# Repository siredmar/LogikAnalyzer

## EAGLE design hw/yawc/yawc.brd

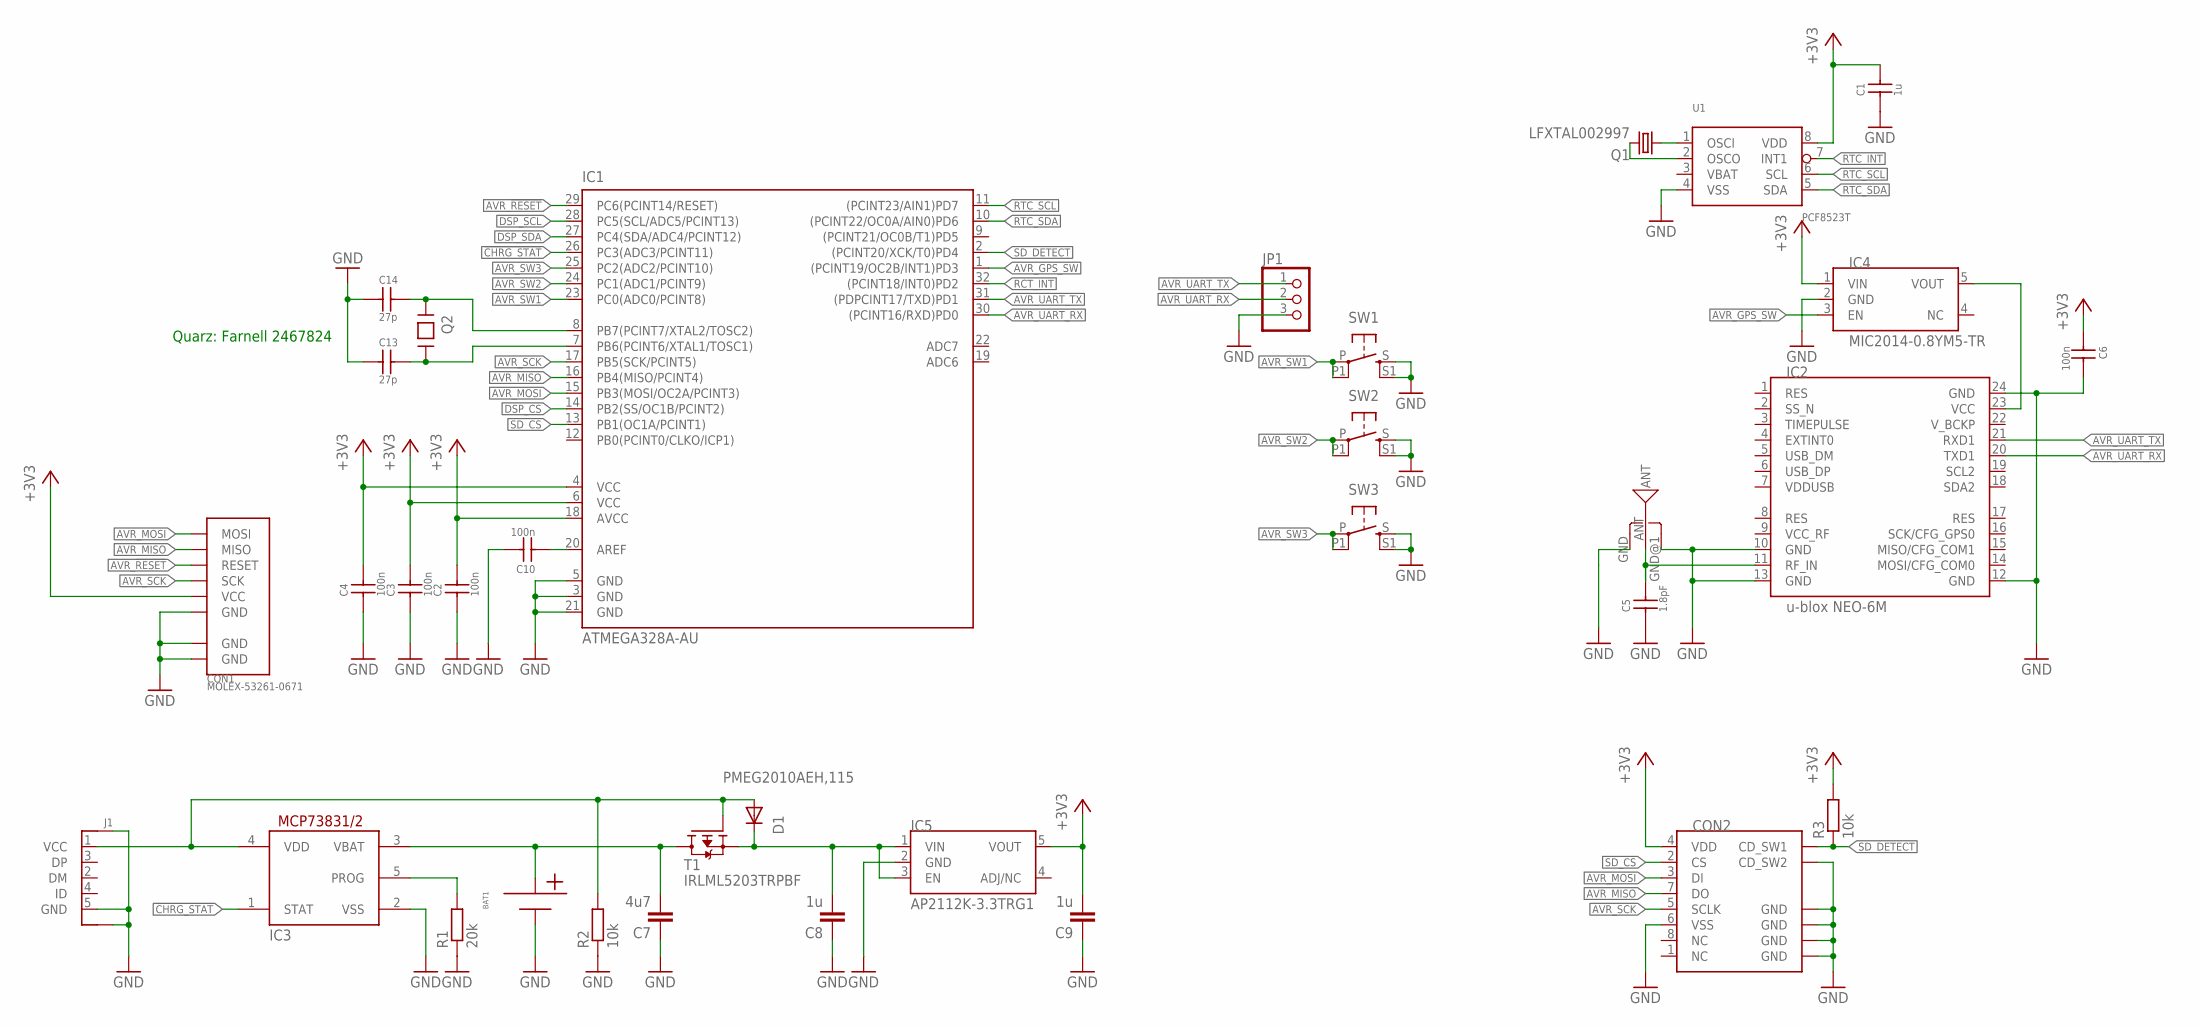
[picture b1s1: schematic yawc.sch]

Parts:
BAT1: LIPO_1S; LIPO_1S_SOLDER_CON
C1: 1u; C0603
C2, C3, C4, C6, C10: 100n; C0603
C5: 1.8pF; C0603
C7: 4u7; C0805
C8, C9: 1u; C0805
C13, C14: 27p; C0603
CON1: MOLEX-53261-0671
CON2: MICRO_SD_1140084168
D1: PMEG2010AEH,115; SOD123
IC1: ATMEGA328A-AU; TQFP32
IC2: u-blox NEO-6M; NEO-6
IC3: MCP73831/OT; SOT23-5L
IC4: MIC2014-0.8YM5-TR; SOT-23-5
IC5: AP2112K-3.3TRG1; SOT-23-5
J1: XM7D-0512
JP1: PINHD-1X3; 1X03
Q1: LFXTAL002997; TC26H
Q2: 16MHz; CRYSTAL-ABRACON-ABM7-SMD
R1: 20k; R0603
R2, R3: 10k; R0603
SW1, SW2, SW3: ALPS_SKHHLNA010
T1: IRLML5203TRPBF; SOT23
U1: PCF8523T; SOT96-1
U$1: ANT_W3011PULSE_1575MHZ; ANT4MMX4.25MM

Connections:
!CHRG_STAT: IC1.26 (PC3(ADC3/PCINT11)), IC3.1 (STAT)
+3V3: C1.2, C2.2, C3.2, C4.2, C6.1, C9.2, CON1.5 (VCC), CON2.4 (VDD), IC1.4 (VCC), IC1.6 (VCC), IC1.18 (AVCC), IC4.1 (VIN), IC5.5 (VOUT), R3.2, U1.8 (VDD)
AVR_!RESET: CON1.3 (RESET), IC1.29 (PC6(PCINT14/RESET))
AVR_GPS_SW: IC1.1 ((PCINT19/OC2B/INT1)PD3), IC4.3 (EN)
AVR_MISO: CON1.2 (MISO), CON2.7 (DO), IC1.16 (PB4(MISO/PCINT4))
AVR_MOSI: CON1.1 (MOSI), CON2.3 (DI), IC1.15 (PB3(MOSI/OC2A/PCINT3))
AVR_SCK: CON1.4 (SCK), CON2.5 (SCLK), IC1.17 (PB5(SCK/PCINT5))
AVR_SW1: IC1.23 (PC0(ADC0/PCINT8)), SW1.P, SW1.P1
AVR_SW2: IC1.24 (PC1(ADC1/PCINT9)), SW2.P, SW2.P1
AVR_SW3: IC1.25 (PC2(ADC2/PCINT10)), SW3.P, SW3.P1
AVR_UART_RX: IC1.30 ((PCINT16/RXD)PD0), IC2.20 (TXD1), JP1.2
AVR_UART_TX: IC1.31 ((PDPCINT17/TXD)PD1), IC2.21 (RXD1), JP1.1
DSP_CS: IC1.14 (PB2(SS/OC1B/PCINT2))
DSP_SCL: IC1.28 (PC5(SCL/ADC5/PCINT13))
DSP_SDA: IC1.27 (PC4(SDA/ADC4/PCINT12))
GND: BAT1.P$1 (+), C1.1, C2.1, C3.1, C4.1, C5.1, C6.2, C7.1, C8.1, C9.1, C10.2, C13.1, C14.1, CON1.6 (GND), CON1.GND@1 (GND), CON1.GND@2 (GND), CON2.6 (VSS), CON2.CD@2 (CD_SW2), CON2.GND@1 (GND), CON2.GND@2 (GND), CON2.GND@3 (GND), CON2.GND@4 (GND), IC1.3 (GND), IC1.5 (GND), IC1.21 (GND), IC2.10 (GND), IC2.12 (GND), IC2.13 (GND), IC2.24 (GND), IC3.2 (VSS), IC4.2 (GND), IC5.2 (GND), J1.5 (GND), J1.P$8 (GND), J1.P$9 (GND), JP1.3, R1.1, R2.1, SW1.S, SW1.S1, SW2.S, SW2.S1, SW3.S, SW3.S1, U1.4 (VSS), U$1.GND, U$1.GND@1 (GND)
unnamed: Q1.1, U1.1 (OSCI)
unnamed: Q1.2, U1.2 (OSCO)
unnamed: C5.2, IC2.11 (RF_IN), U$1.ANT
unnamed: C13.2, IC1.7 (PB6(PCINT6/XTAL1/TOSC1)), Q2.P$2
unnamed: C10.1, IC1.20 (AREF)
unnamed: C14.2, IC1.8 (PB7(PCINT7/XTAL2/TOSC2)), Q2.P$1
unnamed: IC2.23 (VCC), IC4.5 (VOUT)
unnamed: IC3.5 (PROG), R1.2
unnamed: D1.A, IC3.4 (VDD), J1.1 (VCC), R2.2, T1.1 (G)
unnamed: BAT1.P$2 (-), C7.2, IC3.3 (VBAT), T1.3 (D)
unnamed: C8.2, D1.C, IC5.1 (VIN), IC5.3 (EN), T1.2 (S)
RCT_INT: IC1.32 ((PCINT18/INT0)PD2)
RTC_INT: U1.7 (INT1)
RTC_SCL: IC1.11 ((PCINT23/AIN1)PD7), U1.6 (SCL)
RTC_SDA: IC1.10 ((PCINT22/OC0A/AIN0)PD6), U1.5 (SDA)
SD_CS: CON2.2 (CS), IC1.13 (PB1(OC1A/PCINT1))
SD_DETECT: CON2.CD@1 (CD_SW1), IC1.2 ((PCINT20/XCK/T0)PD4), R3.1
VBAT: U1.3 (VBAT)

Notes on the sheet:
Quarz: Farnell 2467824

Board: 2 copper layers, 34 parts (1 on the bottom side), 28 nets, no tracks yet.

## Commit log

2017-05-25 initial git commi
2017-05-25 removed old project content
2017-05-25 modified Readme
2017-05-26 plotting library rudimentary working
